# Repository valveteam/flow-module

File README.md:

# flow-module PCB and Schematic

This repository contains
* Schematics for flow control module.
* PCBs which were designed.
* All files required to manufacture this PCB. 

Note that there is an error in one PCB: the ground plate for the L298P chip should be conneted to the ground plane but it is not. This was remedied by scratching tracks and hand-soldering solder-bridges.

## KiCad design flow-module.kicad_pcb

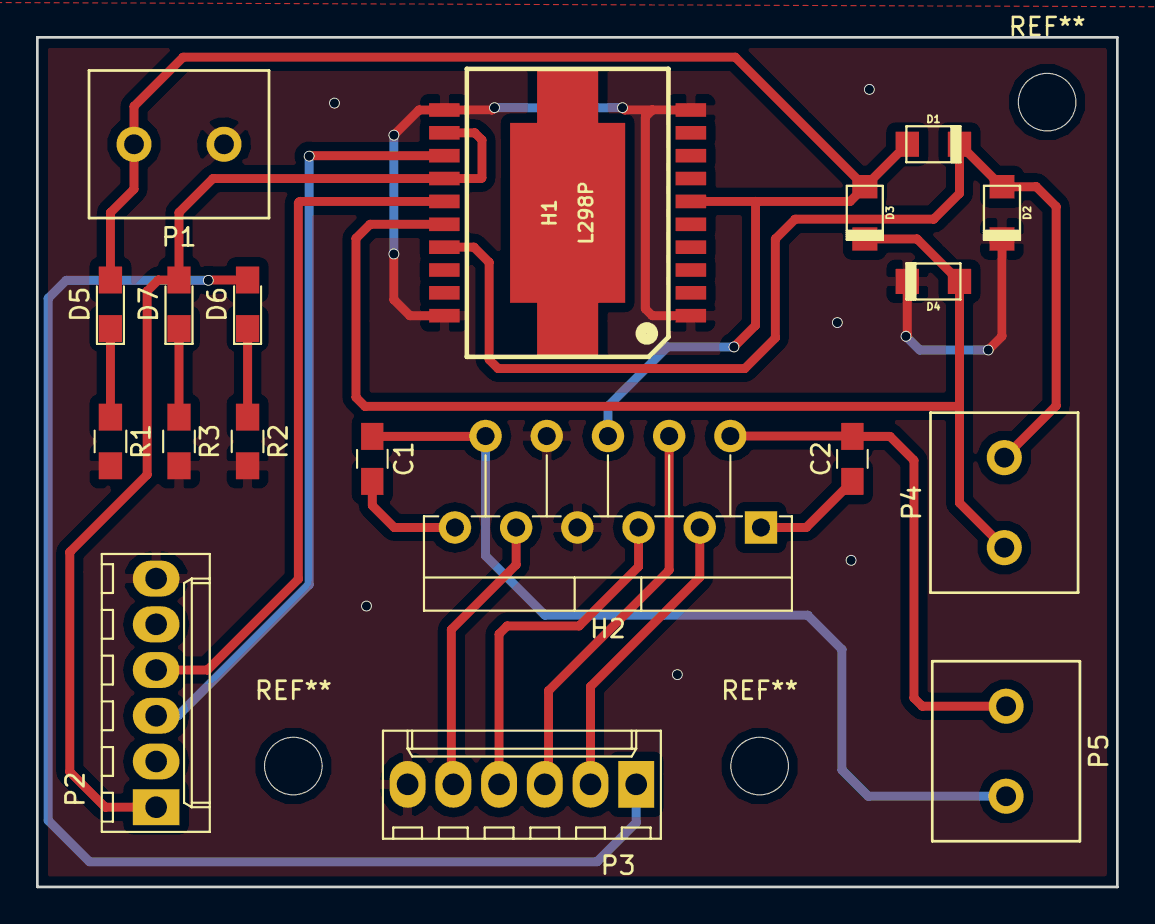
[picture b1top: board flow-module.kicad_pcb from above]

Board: 2 copper layers, 60.0 x 47.2 mm, 19 parts (0 on the bottom side), 19 nets.

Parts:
C1, C2: C; C_0805_HandSoldering
D1, D2, D3, D4: D; do219ab
D5: VCC; LED_0805_HandSoldering
D6: VAA; LED_0805_HandSoldering
D7: VSS; LED_0805_HandSoldering
H1: L298P; powerso-20
H2: LMD18201T; TO-220-11
P1: 12V; TE_TERM
P2: tL298P; Molex_KK-6410-06_06x2.54mm_Straight
P3: tLMD...; Molex_KK-6410-06_06x2.54mm_Straight
P4: fL298P; TE_TERM
P5: fLMD...; TE_TERM
R1: 680; R_0805_HandSoldering
R2, R3: 330; R_0805_HandSoldering

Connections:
Brake: H2.4, P3.3
Dir: H2.3, P3.2
Earth: D2.2, D4.2, H1.1, H1.10, H1.11, H1.20, H2.7, H2.8, P1.2, P2.6, P3.6, R1.2, R2.2, R3.2
Flag: H2.9, P3.5
Input3: H1.13, P2.3
Input4: H1.15, P2.4
unnamed: C1.2, H2.11
unnamed: C2.1, H2.1
unnamed: D1.2, D2.1, H1.17, P4.1
unnamed: D3.2, D4.1, H1.16, P4.2
unnamed: D5.1, R1.1
unnamed: D6.1, R2.1
unnamed: D7.1, R3.1
Output1: C2.2, H2.2, P5.2
Output2: C1.1, H2.10, P5.1
PWM: H2.5, P3.4
VAA: D6.2, P3.1
VCC: D1.1, D3.1, D5.2, H1.6, H2.6, P1.1
VSS: D7.2, H1.12, H1.14, P2.1

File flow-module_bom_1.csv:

Component,Description,Part,References,Value,Footprint,Quantity Per PCB,Datasheet
1,Unpolarized capacitor,C,C1 C2,C,C_0805_HandSoldering,2,
2,Diode,D,D1 D2 D3 D4,D,do219ab,4,
3,,LED-RESCUE-flow-module,D5 D6 D7,LED,LED_0805_HandSoldering,3,
4,,L298P,H1,L298P,powerso-20,1,
5,,LMD18201T,H2,LMD18201T,TO-220-11,1,
6,,CONN_01X06,P2 P3,MOLEX_01X06,Molex_KK-6410-06_06x2.54mm_Straight,2,
7,,CONN_01X02,P1 P4 P5,TERM_01X02,TE_TERM,3,
8,Resistor,R,R2 R3,330,R_0805_HandSoldering,2,
9,Resistor,R,R1,680,R_0805_HandSoldering,1,





Component Groups:,9
Component Count:,19
Fitted Components:,19
Number of PCBs:,1
Total components:,19
Schematic Version:,1
Schematic Date:,2018-05-22
BoM Date:,04/06/2018 09:51:26
Schematic Source:,C:/Users/tooyi/Dropbox/tfpb/flow-module/flow-module.sch
KiCad Version:,Eeschema 4.0.7

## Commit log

2018-05-22 Initial schematical and basic files.
2018-05-23 Added status LEDs to the schematic.
2018-05-23 Associate components and update the netlist.
2018-05-23 Made PCB.
2018-05-23 Add more vias between ground planes.
2018-05-23 Files for PCB production (added for reference).
2018-06-04 Documentation
